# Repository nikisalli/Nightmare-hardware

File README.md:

# Nightmare-hardware
Nightmare-hardware

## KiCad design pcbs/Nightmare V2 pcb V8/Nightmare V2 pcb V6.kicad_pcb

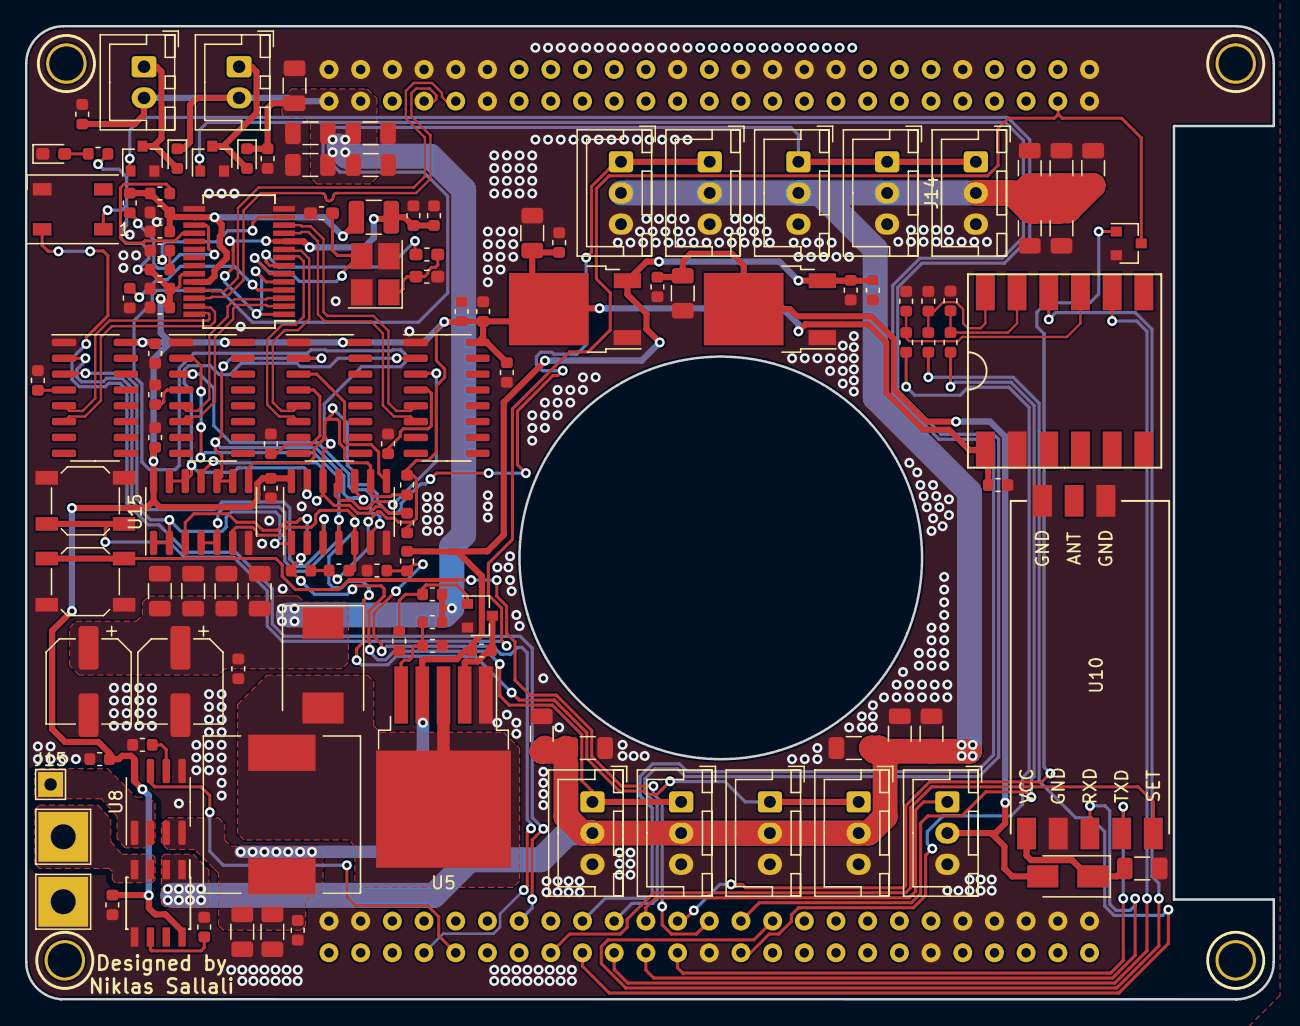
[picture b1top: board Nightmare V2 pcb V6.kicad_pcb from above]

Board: 2 copper layers, 100.0 x 78.0 mm, 130 parts (0 on the bottom side), 73 nets.

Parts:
C1, C4, C16, C23, C24, C25, C26, C27, C30, C38, C39, C41, C42, C43, C44, C45, C46, C47, C48, C49, C50, C51, C53, C54: 10u; C_1206_3216Metric
C2, C3, C5, C7, C8, C9, C10, C11, C12, C13, C14, C15, C20, C21, C22, C28, C29, C33, C34, C35, C36, C37, C40, C52, C58: 100n; C_0603_1608Metric
C6, C57: 1n; C_0603_1608Metric
C17, C18, C19: 1u; C_0603_1608Metric
C31, C32: 22p; C_0603_1608Metric_Pad1.05x0.95mm_HandSolder
C55, C56: 220u; CP_Elec_6.3x3.9
D1: SS510; D_SMC
D4: LED; LED_0603_1608Metric_Pad1.05x0.95mm_HandSolder
D5: 1N5819; D_SMA
D8, D11: 1N5819; D_0603_1608Metric
J1, J2: Conn_01x01_Male; TestPoint_THTPad_4.0x4.0mm_Drill2.0mm
J3, J4: Conn_01x02_Male; JST_XH_B2B-XH-A_1x02_P2.50mm_Vertical
J5, J6, J7, J8, J9, J10, J11, J12, J13, J14: 01x03; JST_XH_B3B-XH-A_1x03_P2.50mm_Vertical
J15: Conn_01x01_Male; TestPoint_THTPad_2.0x2.0mm_Drill1.0mm
L1: 33uH; L_12x12mm_H6mm
L2: 10u; L_1210_3225Metric
LED1: ws2812b; LED_WS2812B_PLCC4_5.0x5.0mm_P3.2mm
MK1, MK2, MK3, MK4: Mounting_Hole; MOUNTING_HOLE_M2.5
Q1, Q6, Q7, Q8: 2N7002; SOT-23
R1: R; R_0603_1608Metric
R4, R13, R14, R17: 10k; R_0603_1608Metric
R5: 91k; R_0603_1608Metric
R6, R7, R18, R22, R23, R29, R32, R33: 1k; R_0603_1608Metric
R8: 3.6k; R_0603_1608Metric
R9: 500R; R_0603_1608Metric
R12: 1.5k; R_0603_1608Metric
R15: 680R; R_0603_1608Metric
R16: 100k; R_0603_1608Metric
R21: 220R; R_0603_1608Metric_Pad1.05x0.95mm_HandSolder
R28, R30, R31: 2k; R_0603_1608Metric
SW1, SW2: SW_Push; SW_SPST_SKQG_WithoutStem
U1, U8: ACS712; SOIC-8_3.9x4.9mm_P1.27mm
U2, U3, U7, U13: CH340G; SOIC-16_3.9x9.9mm_P1.27mm
U4: lattepanda_alpha
U5: XL6009; TO-263-5_TabPin3
U6, U14: AZ1117-5.0; TO-252-2
U9: GL850G; SSOP-28_5.3x10.2mm_P0.65mm
U10: HC-12
U11: gy953_imu; GY953_IMU
U12: 74LS126; SOIC-14_3.9x8.7mm_P1.27mm
U15: 74LS125; SOIC-14_3.9x8.7mm_P1.27mm
Y1: 12Mhz; Crystal_SMD_SeikoEpson_TSX3225-4Pin_3.2x2.5mm_HandSoldering

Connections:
3.3V: C15.1, C19.1, L2.1, R14.1, R16.1, U9.16, U9.24
+5V: C7.1, C8.1, C9.1, C12.1, C14.1, C16.1, C18.1, C28.1, C29.1, C34.1, C36.1, C37.1, C58.1, LED1.1, R6.1, R7.1, R12.1, R13.1, R22.1, R23.1, U1.8, U2.16, U3.16, U7.16, U8.8, U9.23, U11.1, U12.14, U13.16, U14.2, U15.14
+5VA: C52.1, C53.1, D5.2, J11.2, U6.2
+BATT: J1.1, U1.3, U1.4
BAT_M: R17.2, R18.1, U4.22
CPU_SW: Q6.1, U4.39
CUR_M: U4.21, U8.7
D1+: U2.5, U9.28
D1-: U2.6, U9.27
D2+: U3.5, U9.3
D2-: U3.6, U9.2
D3+: U7.5, U9.9
D3-: U7.6, U9.8
D4+: U9.12, U13.5
D4-: U9.11, U13.6
D+: U4.72, U9.26
D-: U4.71, U9.25
FAN1: Q7.1, U4.41
FAN2: Q8.1, U4.42
GND: C1.2, C2.2, C3.2, C4.2, C5.2, C6.2, C7.2, C8.2, C9.2, C10.2, C11.2, C12.2, C13.2, C14.2, C15.2, C16.2, C17.2, C18.2, C19.2, C20.2, C21.2, C22.2, C23.2, C24.2, C25.2, C26.2, C27.2, C28.2, C29.2, C30.2, C31.2, C32.2, C33.2, C34.2, C35.2, C36.2, C37.2, C38.2, C39.2, C40.2, C41.2, C42.2, C43.2, C44.2, C45.2, C46.2, C47.2, C48.2, C49.2, C50.2, C51.2, C52.2, C53.2, C54.2, C55.2, C56.2, C57.2, C58.2, D4.1, J2.1, J5.3, J6.3, J7.3, J8.3, J9.3, J10.3, J11.3, J12.3, J13.3, J14.3, LED1.3, Q1.2, Q6.2, Q7.2, Q8.2, R4.2, R9.2, R15.2, R18.2, R28.2, R30.2, R31.2, SW1.1, SW2.1, U1.5, U2.1, U3.1, U4.6, U4.13, U4.26, U4.27, U4.28, U4.29, U4.30, U4.49, U4.50, U4.51, U4.70, U4.76, U4.80, U4.84, U4.85, U4.86, U4.87, U4.89, U4.95, U4.96, U4.97, U4.98, U4.99, U4.100, U5.1, U6.1, U7.1, U8.5, U9.14, U9.15, U10.2, U10.6, U10.8, U11.2, U12.7, U13.1, U14.1, U15.7, Y1.2, Y1.4
H_RX: U4.15, U10.3
H_TX: U4.14, U10.4
INT: U4.16, U11.8
IO4: LED1.4, U4.44
IO11: U4.18, U10.5
IO12: J11.1, U4.40
unnamed: C2.1, U2.4
unnamed: C3.1, U3.4
unnamed: C6.1, U8.6
unnamed: C13.1, C17.1, L2.2, U9.1, U9.5, U9.10
unnamed: C20.1, U7.4
unnamed: C21.1, U13.4
unnamed: C22.1, R13.2, U9.13
unnamed: C31.1, R21.2, Y1.1
unnamed: C32.1, U9.6, Y1.3
unnamed: C54.1, D5.1, U10.1
unnamed: C57.1, U1.6
unnamed: D1.2, L1.1, U5.3
unnamed: D4.2, R12.2
unnamed: D8.2, J3.1, Q7.3
unnamed: D11.2, J4.1, Q8.3
unnamed: Q1.3, R1.2, U5.2
unnamed: R4.1, R5.2, U5.5
unnamed: R14.2, U9.17
unnamed: R15.1, U9.4
unnamed: R16.2, U9.18
unnamed: R21.1, U9.7
unnamed: R28.1, R29.2, U11.11
unnamed: R30.1, R32.2, U11.12
unnamed: R31.1, R33.2, U11.9
RESET: SW2.2, U4.38
SW: Q6.3, SW1.2, U4.52
S_CS: R32.1, U4.17
S_MISO: U4.36, U11.10
S_MOSI: R33.1, U4.12
S_SCK: R29.1, U4.37
S_SERIAL1: J5.1, J6.1, R6.2, U12.2, U15.3
S_SERIAL2: J7.1, J8.1, R7.2, U12.5, U15.6
S_SERIAL3: J9.1, J10.1, R22.2, U12.9, U15.8
S_SERIAL4: J12.1, J13.1, J14.1, R23.2, U12.12, U15.11
USB_RX1: U2.3, U12.3
USB_RX2: U3.3, U12.6
USB_RX3: U7.3, U12.8
USB_RX4: U12.11, U13.3
USB_TX1: U2.2, U12.1, U15.1, U15.2
USB_TX2: U3.2, U12.4, U15.4, U15.5
USB_TX3: U7.2, U12.10, U15.9, U15.10
USB_TX4: U12.13, U13.2, U15.12, U15.13
VAA: C1.1, C4.1, C5.1, C10.1, C33.1, L1.2, R1.1, R17.1, U5.4, U6.3, U8.3, U8.4, U14.3
VBUS: C42.1, C43.1, C44.1, C45.1, C46.1, C47.1, C48.1, C49.1, C50.1, C51.1, J5.2, J6.2, J7.2, J8.2, J9.2, J10.2, J12.2, J13.2, J14.2, U1.1, U1.2
VDD: C11.1, C23.1, C24.1, C25.1, C26.1, C27.1, C30.1, C35.1, C38.1, C39.1, C40.1, C41.1, C55.1, C56.1, D1.1, D8.1, D11.1, J3.2, J4.2, R5.1, R8.1, U4.74, U4.75
V_BATT: J15.1, U8.1, U8.2
V_LIM: Q1.1, R8.2, R9.1

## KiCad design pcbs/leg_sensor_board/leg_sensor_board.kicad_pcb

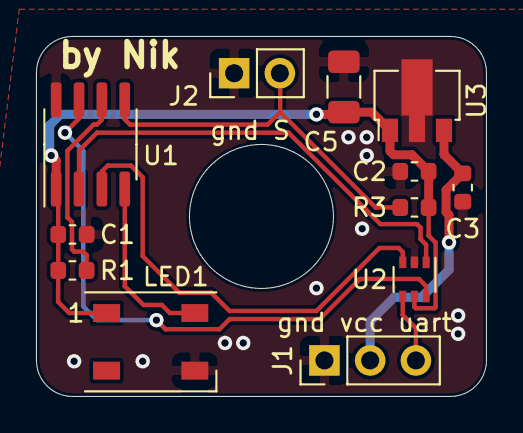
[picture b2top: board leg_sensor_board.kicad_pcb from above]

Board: 2 copper layers, 25.0 x 20.0 mm, 12 parts (0 on the bottom side), 10 nets.

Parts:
C1, C2: C; C_0603_1608Metric
C3: 100n; C_0603_1608Metric
C5: 10u; C_1206_3216Metric
J1: Conn_01x03; PinHeader_1x03_P2.54mm_Vertical
J2: Conn_01x02; PinHeader_1x02_P2.54mm_Vertical
LED1: ws2812b; LED_WS2812B_PLCC4_5.0x5.0mm_P3.2mm
R1, R3: 10k; R_0603_1608Metric
U1: ATtiny202-SS; SOIC-8_3.9x4.9mm_P1.27mm
U2: FSA3157P6X; SOT-363_SC-70-6
U3: L78L05_SOT89; SOT-89-3

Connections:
GND: C1.2, C2.2, C3.2, C5.2, J1.1, J2.1, LED1.3, U1.8, U2.2, U3.2
unnamed: LED1.4, U1.4
unnamed: R1.2, U1.6
unnamed: U1.2, U2.1
unnamed: U1.3, U2.3
unnamed: U1.7, U2.6
SENS+: J2.2, R3.2, U1.5
UART: J1.3, U2.4
VBUS: C3.1, J1.2, U3.3
VCC: C1.1, C2.1, C5.1, LED1.1, R1.1, R3.1, U1.1, U2.5, U3.1

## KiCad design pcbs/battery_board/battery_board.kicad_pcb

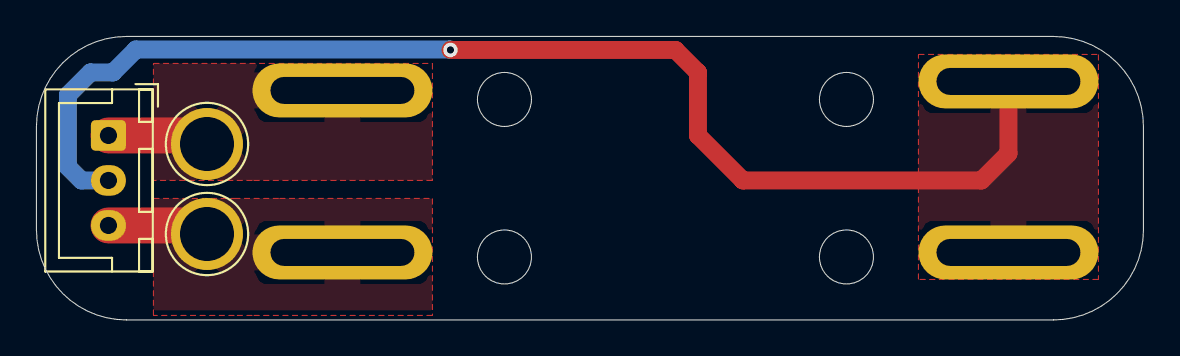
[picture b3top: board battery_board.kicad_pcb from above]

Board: 2 copper layers, 61.5 x 15.8 mm, 11 parts (0 on the bottom side), 3 nets.

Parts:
J1: Conn_01x03; JST_XH_B3B-XH-A_1x03_P2.50mm_Vertical
MK1, MK2, MK3, MK4: Mounting_Hole; MountingHole_3mm
TP1: C2+; lipo_conductor_slit
TP2: C2-; lipo_conductor_slit
TP3: C1+; lipo_conductor_slit
TP4: C1-; lipo_conductor_slit
TP9: OUT+; TestPoint_Plated_Hole_D3.0mm
TP10: OUT-; TestPoint_Plated_Hole_D3.0mm

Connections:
BATT+: J1.1, TP1.1, TP9.1
BATT-: J1.3, TP4.1, TP10.1
MID: J1.2, TP2.1, TP3.1

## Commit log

2021-04-25 added hardware
